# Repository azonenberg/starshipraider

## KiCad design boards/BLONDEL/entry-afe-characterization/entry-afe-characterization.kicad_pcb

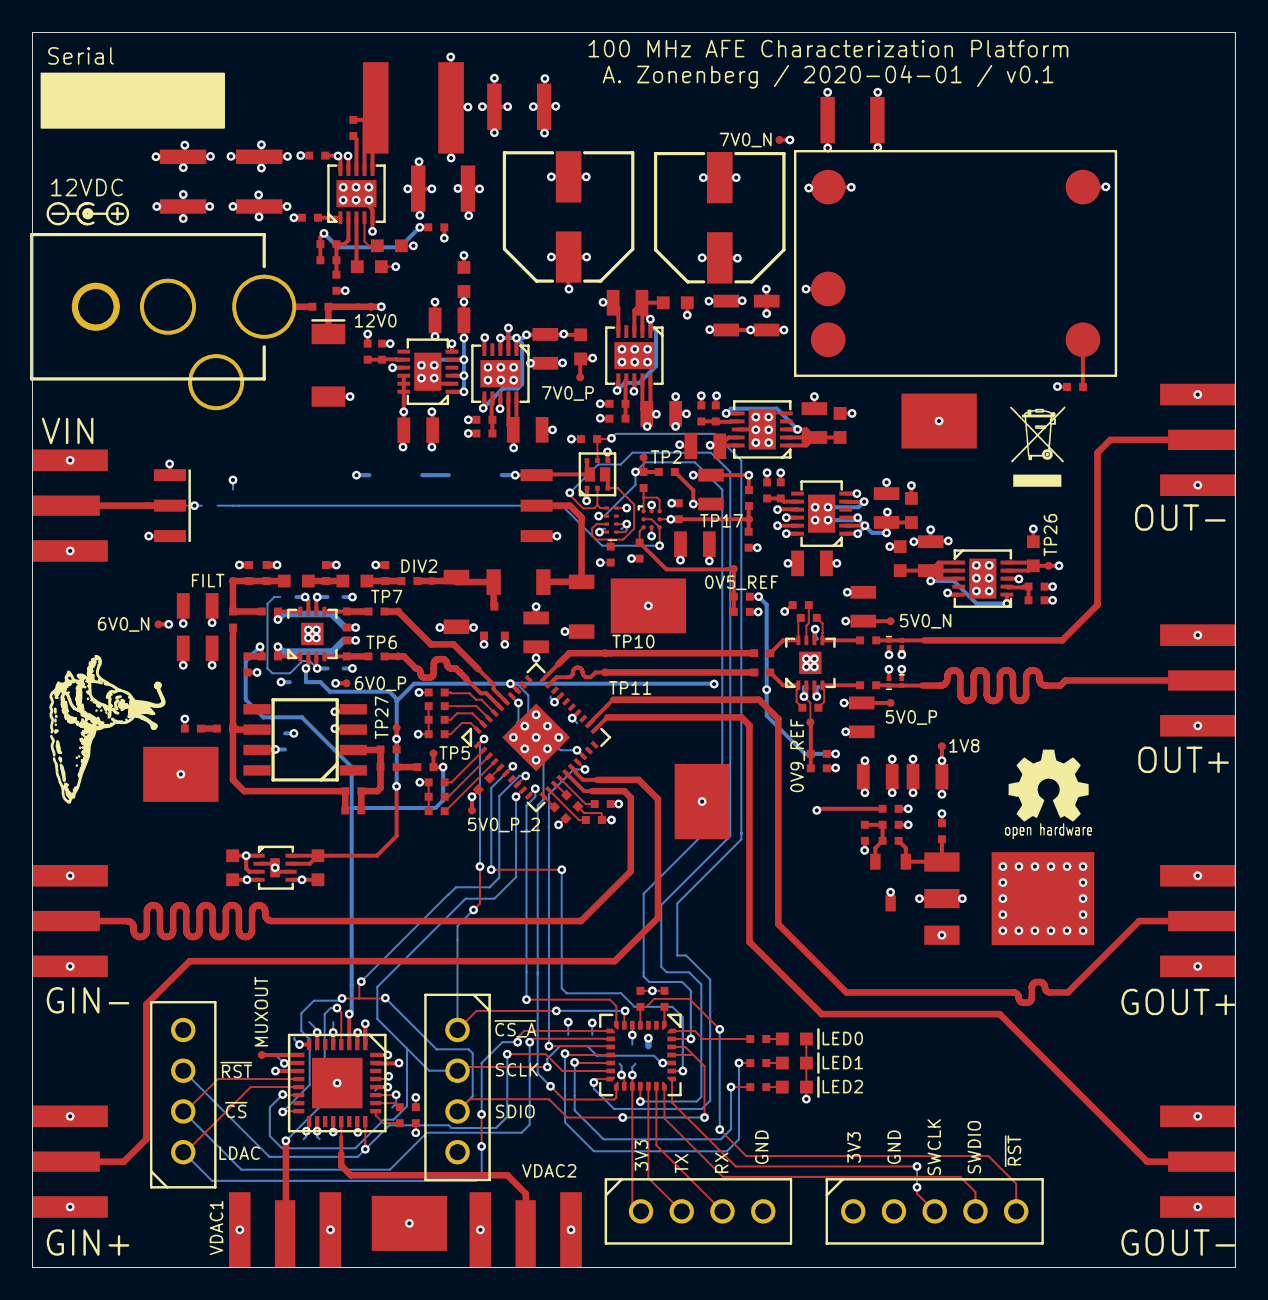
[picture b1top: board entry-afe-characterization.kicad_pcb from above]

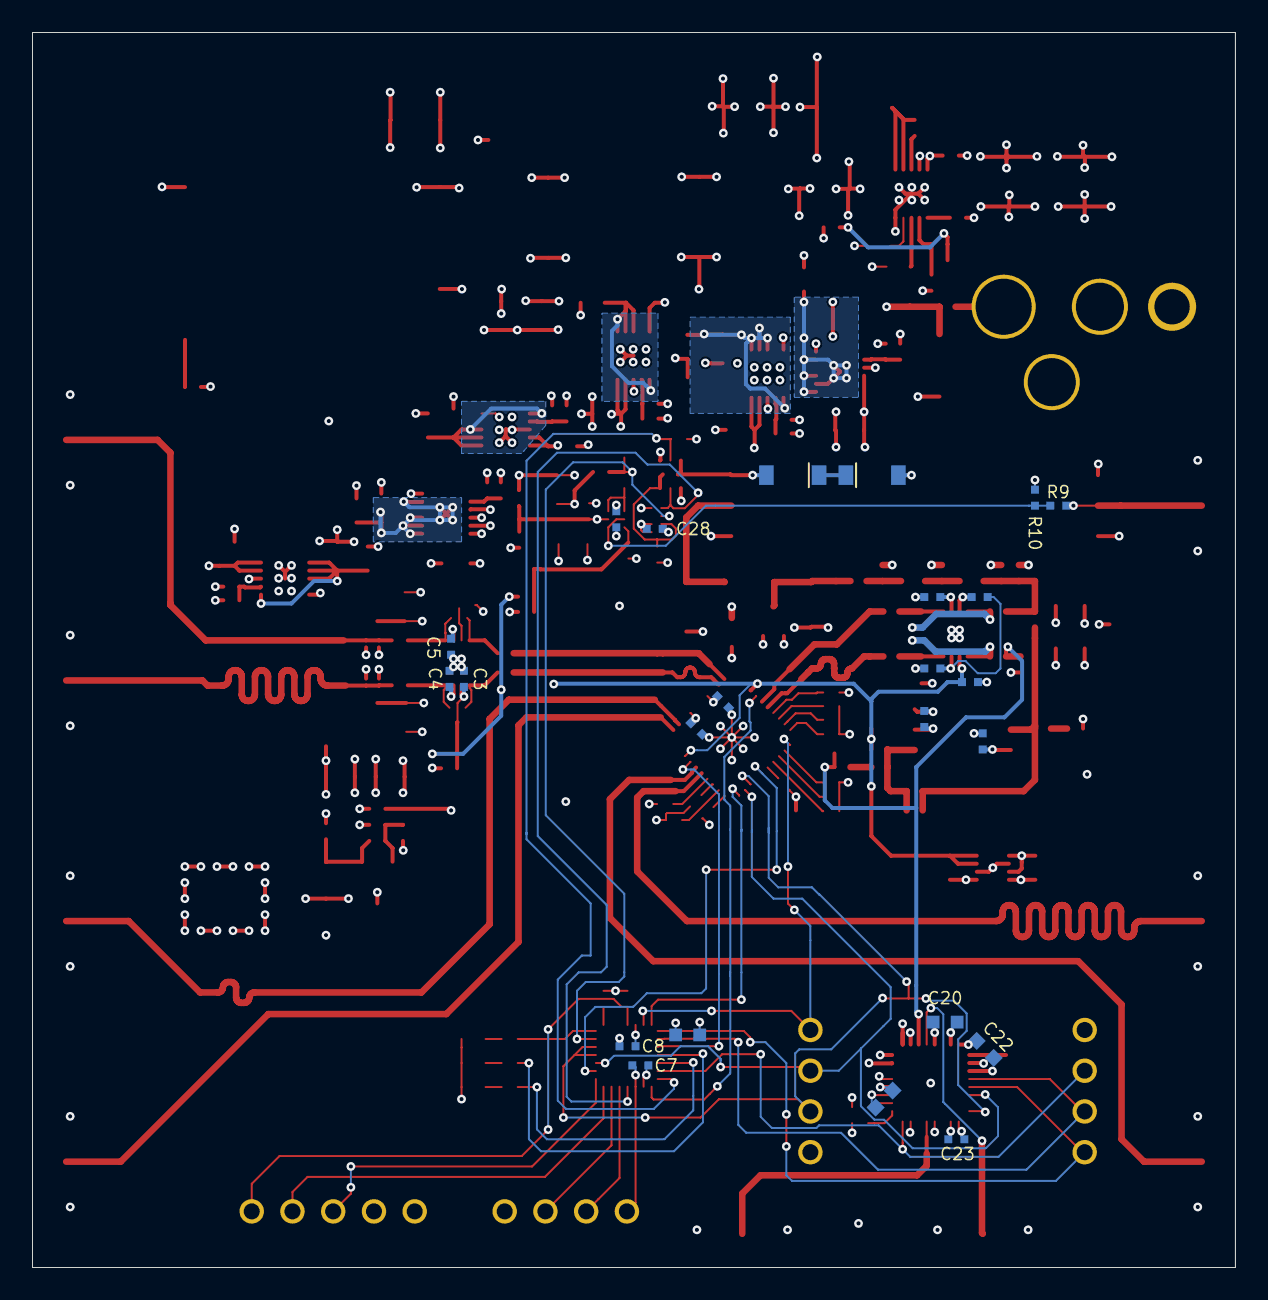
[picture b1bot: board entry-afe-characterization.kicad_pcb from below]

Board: 4 copper layers, 75.0 x 77.0 mm, 226 parts (24 on the bottom side), 116 nets.

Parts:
C1: 13 pF; EIA_0402_CAP_NOSILK
C2: 27 pF; EIA_0402_CAP_NOSILK
C3, C7, C8, C15, C28, C42, C43, C46, C73, C74: 0.47 uF; EIA_0402_CAP_NOSILK
C4, C5, C18, C19, C50, C59, C60, C66, C67: 0.47 uF 25V; EIA_0402_CAP_NOSILK
C6, C45: 4.7 uF; EIA_0603_CAP_NOSILK
C9, C13, C14, C23, C24, C25, C26, C32, C37, C68, C69: 0.1 uF; EIA_0402_CAP_NOSILK
C10, C11, C12, C27, C71, C72: 4.7 uF; EIA_0805_CAP_NOSILK
C16: 75 pF; EIA_0402_CAP_NOSILK
C17, C38, C39, C40, C41, C44, C51, C52, C55, C56, C57, C58, C61, C62: 4.7 uF 50V; EIA_0805_CAP_NOSILK
C20, C21, C22, C33: 1 uF; EIA_0603_CAP_NOSILK
C29, C30, C54: 10 uF; EIA_1210_CAP_NOSILK
C31: 3300 pF; EIA_0603_CAP_NOSILK
C34, C35: 22 uF; EIA_1210_CAP_NOSILK
C36: 10 pF; EIA_0402_CAP_NOSILK
C47: 2.2 uF; EIA_0603_CAP_NOSILK
C48: 330 pF; EIA_0603_CAP_NOSILK
C49, C53: 220 uF; CAP_AL_6.3MM_SMT
C63: 22 pF; EIA_0402_CAP_NOSILK
C64, C65: 22 uF; EIA_0805_CAP_NOSILK
C70: DNP; EIA_0402_CAP_NOSILK
D1: PDZ10BGWX; SOD123
D2: BAS21GWJ; SOD123
D3: NUP1301U; SOT323_3
D4, D5, D6, D7: NSR01F30MXT5G; DFN_2_0.62x0.32
D8: SMBJ12A; SMB
D9, D10, D11: GREEN; EIA_0603_LED
F1: 1A; EIA_0402_RES_NOSILK
FB1, FB2, FB3, FB4, FB5, FB6: MI0603J601R-10; EIA_0603_INDUCTOR_NOSILK
J1, J2, J3, J4, J5, J6, J7, J13, J14: SMA; CONN_SMA_EDGE_SAMTEC_SMA_J_P_H_ST_EM1
J8: Conn_01x05; CONN_HEADER_2.54MM_1x5
J9, J11, J12: Conn_01x04; CONN_HEADER_2.54MM_1x4
J10: CONN_3_PWROUT; CONN_CUI_PJ-058BH_HIPWR_BARREL_NOSLOT
K1: 9202-12-00; RELAY_COTO_9202
L1: 11 nH; EIA_0402_RES_NOSILK
L2: 51 nH; EIA_0603_INDUCTOR_NOSILK
L3: 91 nH; EIA_0603_INDUCTOR_NOSILK
L4: 4.7 uH; INDUCTOR_YUDEN_NR6028
Q1: SSM6N58NU; DFN_6_0.65MM_2x2MM_GDS
Q2: 2SA2039-TL-E; TO_253
R1, R3: CRCW1206150RFKEAHP; EIA_1206_CAP_NOSILK
R2: CRCW120637R4FKEAHP; EIA_1206_CAP_NOSILK
R4: 68 0.1%; EIA_0402_RES_NOSILK
R5, R6, R7, R8, R62: 330 0.1%; EIA_0402_RES_NOSILK
R9: 9.1K 1%; EIA_0402_RES_NOSILK
R10, R55: 1K 1%; EIA_0402_RES_NOSILK
R11, R12, R15, R16, R17, R18, R19, R20, R21, R22, R23, R24, R25, R26, R27, R34, R35, R36: 10K; EIA_0402_RES_NOSILK
R13, R14: 100 0.1%; EIA_0402_RES_NOSILK
R28, R29: 127 0.1%; EIA_0402_RES_NOSILK
R30, R31, R32, R33: 49.9; EIA_0402_RES_NOSILK
R37, R53: 1K; EIA_0402_RES_NOSILK
R38: 22.1K; EIA_0402_RES_NOSILK
R39: 180K; EIA_0402_RES_NOSILK
R40, R52: 470 1%; EIA_0402_RES_NOSILK
R41: 4.7K 1%; EIA_0402_RES_NOSILK
R42, R57, R58: 49.9K 1%; EIA_0402_RES_NOSILK
R43, R56: 60.4K 1%; EIA_0402_RES_NOSILK
R44, R63: 0; EIA_0402_RES_NOSILK
R45: 2.7K 1%; EIA_0402_RES_NOSILK
R46: 33K 1%; EIA_0402_RES_NOSILK
R47: 6.49K 1%; EIA_0402_RES_NOSILK
R48: 3.6K 1%; EIA_0402_RES_NOSILK
R49: 8.06K 1%; EIA_0402_RES_NOSILK
R50: 2K 1%; EIA_0402_RES_NOSILK
R51: 11.5K 1%; EIA_0402_RES_NOSILK
R54: 9.09K 1%; EIA_0402_RES_NOSILK
R59, R60, R64: 20K 0.1%; EIA_0402_RES_NOSILK
R61: 10K 0.1%; EIA_0402_RES_NOSILK
R65, R66, R67: 470; EIA_0402_RES_NOSILK
TP1, TP2, TP3, TP5, TP6, TP7, TP10, TP11, TP12, TP13, TP17, TP18, TP19, TP20, TP21, TP22, TP23, TP24, TP25, TP26, TP27, TP28, TP29: TESTPOINT; TESTPOINT_SMT_0.5MM
TP4, TP8, TP9, TP14, TP15: TESTCLIP; TESTPOINT_SMT_KEYSTONE_5016
U1, U6: LMH6552; DFN_8_0.5MM_3x3MM
U2: ADL5205; QFN_40_0.5MM_6x6MM
U3: LM393-DSBGA8; BGA_8_2x2_DEPOP1_0.5MM_TI_YZR
U4: STM32F031G6U6TR; QFN_28_0.5MM_4x4MM_NOPAD
U5: LTC2664; QFN_32_0.5MM_5x5MM
U7: 74LVC1G74-XSON8; DFN_8_0.5MM_2x1MM
U8: TPS54227-DRC; DFN_10_0.5MM_3x3MM
U9, U10, U11, U16: LT3042; DFN_10_0.5MM_3x3MM
U12: MCP1501T-25E/RW; DFN_8_0.5MM_2x2MM
U13, U15: LT3093; DFN_12_0.5MM_3x3MM
U14: PTN78000AAZ; MODULE_TI_PTN78000A
U17: TL431ACDBZR; SOT23_3
U18: OP07; SOIC_8_3.9MM

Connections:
/0V5_REF: C73.1, R49.2, R50.1, TP29.1, U3.C1
/0V9_REF: C3.1, R47.2, R48.1, TP28.1, U6.2
/1V8: C64.1, D4.1, D6.1, Q2.3, R40.2, R41.1, R52.1, TP12.1
/2V5_REF: C15.1, C48.1, R47.1, R49.1, R59.2, TP27.1, U1.2, U2.18, U2.33, U12.7, U12.8
/3V3: C6.1, C7.1, C8.1, C23.1, C45.1, C47.1, J8.1, J9.1, TP26.1, U4.5, U4.17, U5.18, U5.32, U11.9, U11.10, U12.1, U12.3
/5V0_N: C5.1, C9.2, C10.2, C22.1, C58.1, C65.2, C72.1, D3.1, R45.2, R54.1, TP18.1, U3.C2, U5.8, U5.PAD, U6.6, U15.10, U15.11, U15.12, U17.3
/5V0_P: C4.1, C9.1, C10.1, C20.1, C21.1, C27.1, C28.1, C40.1, C71.1, D3.2, R15.2, R36.1, R37.1, R40.1, TP24.1, U3.A2, U5.7, U5.28, U6.3, U7.8, U9.9, U9.10
/5V0_P_2: C17.1, C18.1, C19.1, C62.1, R16.2, R17.2, R26.1, TP25.1, U2.24, U2.27, U16.9, U16.10
/6V0_N: C12.2, C14.2, C57.1, C67.1, TP19.1, U1.6, U13.10, U13.11, U13.12, U18.4
/6V0_P: C11.1, C13.1, C41.1, C50.1, R12.2, TP23.1, U1.3, U10.9, U10.10, U18.7
/12V0: C29.1, C30.1, C37.2, C49.1, C51.1, C52.1, D1.2, D8.1, F1.2, K1.1, R11.2, TP21.1, U8.9, U8.10, U14.2
/Common mode shift/VGAIN_N: R14.2, TP11.1, U2.29
/Common mode shift/VGAIN_P: R13.2, TP10.1, U2.30
/Common mode shift/VOUT_N: D6.2, D7.1, J7.1, R33.1
/Common mode shift/VOUT_P: D4.2, D5.1, J6.1, R32.1
/DAC/DAC_REF: C24.1, U5.25
/DAC/DAC_REF_COMP: C25.1, U5.26
/DAC/MUXOUT: TP13.1, U5.9
/DAC/VDAC1: J13.1, U5.4
/DAC/VDAC2: J14.1, U5.21
/DAC_CS_N: J11.2, U4.9, U5.12
/DAC_LDAC: J11.1, U4.8, U5.13
/DAC_RST_N: J11.3, U4.13, U5.24
/GAIN2_PWRUP: U2.17, U4.10
/GAIN_PWRUP: U2.34, U4.15
/GND: C1.2, C2.2, C3.2, C4.2, C5.2, C6.2, C7.2, C8.2, C11.2, C12.1, C13.2, C14.1, C15.2, C16.2, C17.2, C18.2, C19.2, C20.2, C21.2, C22.2, C23.2, C24.2, C25.2, C26.2, C27.2, C28.2, C29.2, C30.2, C31.2, C33.2, C34.2, C35.2, C37.1, C38.2, C39.2, C40.2, C41.2, C42.2, C43.2, C44.2, C45.2, C46.2, C47.2, C48.2, C49.2, C50.2, C51.2, C52.2, C53.1, C54.2, C55.2, C56.2, C57.2, C58.2, C59.2, C60.2, C61.2, C62.2, C64.2, C65.1, C66.2, C67.2, C68.2, C69.2, C71.2, C72.2, C73.2, C74.2, D5.2, D7.2, D8.2, D9.1, D10.1, D11.1, J1.2, J2.2, J3.2, J4.2, J5.2, J6.2, J7.2, J8.2, J9.4, J10.2, J11.4, J12.4, J13.2, J14.2, K1.5, K1.6, Q1.S1, Q1.S2, Q2.2, Q2.4, R1.2, R3.2, R4.2, R10.2, R18.2, R19.2, R20.2, R21.2, R22.2, R23.2, R24.2, R25.2, R27.1, R34.1, R35.2, R38.2, R42.1, R43.1, R46.1, R48.2, R50.2, R55.2, R56.2, R57.2, R58.1, TP4.1, TP8.1, TP9.1, TP14.1, TP15.1, U1.PAD, U2.PAD, U4.16, U5.1, U5.2, U5.5, U5.10, U5.11, U5.17, U5.20, U5.23, U5.27, U5.29, U5.31, U6.PAD, U7.1, U7.2, U7.4, U8.5, U8.PAD, U9.5, U9.8, U9.PAD, U10.5, U10.8, U10.PAD, U11.5, U11.8, U11.PAD, U12.2, U12.4, U12.5, U12.6, U12.PAD, U13.6, U13.9, U14.5, U15.6, U15.9, U16.5, U16.8, U16.PAD, U18.3
/Gain Stage/GIN_N: J3.1, U2.15
/Gain Stage/GIN_P: J2.1, U2.16
/Gain Stage/GOUT_N: J5.1, U2.21
/Gain Stage/GOUT_P: J4.1, U2.22
/Gain Stage/VSHIFTED_N: R31.1, TP7.1, U2.35
/Gain Stage/VSHIFTED_P: R30.1, TP6.1, U2.36
/INPUT_RST: Q1.G2, R34.2, U4.14
/Input/COIL_N: D2.2, K1.2, Q1.D1
/Input/INPUT_RST_N: Q1.D2, R36.2, U7.7
/Input/VIN: J1.1, K1.3, R9.1
/Input/VIN_DIV2: D3.3, L1.2, R2.1, R3.1, TP1.1
/Input/VIN_DIV10: R9.2, R10.1, U3.B1, U3.C3
/Input/VIN_FILTERED: C16.1, L3.1, R4.1, R5.2, R62.1, TP3.1
/Input/VIN_SWITCHED: K1.4, R1.1, R2.2
/MCU/LED0: R65.2, U4.28
/MCU/LED1: R66.2, U4.11
/MCU/LED2: R67.2, U4.12
/MCU/RST_N: C26.1, J8.5, U4.4
/MCU/SWCLK: J8.3, U4.22
/MCU/SWDIO: J8.4, U4.21
/MCU/UART_RX: J9.3, U4.20
/MCU/UART_TX: J9.2, U4.19
/N0V5_REF: C74.1, R54.2, R55.1, TP17.1, U3.B3
/OVERVOLTAGE_N: R37.2, R53.1, TP2.1, U4.27, U7.6
/Power Supply/5V0_P_2_SET: C66.1, R58.2, U16.7
/Power Supply/5V0_P_SET: C42.1, R42.2, U9.7
/Power Supply/7V0_ADJ: R51.1, U14.4
/Power Supply/7V0_FB: C36.1, R38.1, R39.1, U8.2
/Power Supply/7V0_N: C53.2, C54.1, FB4.2, FB5.2, R51.2, TP20.1, U14.1
/Power Supply/7V0_N_1: C55.1, FB4.1, U13.1, U13.2, U13.3, U13.5, U13.PAD
/Power Supply/7V0_N_2: C56.1, FB5.1, U15.1, U15.2, U15.3, U15.5, U15.PAD
/Power Supply/7V0_P: C34.1, C35.1, FB1.2, FB2.2, FB3.2, FB6.2, L4.1, R44.1, TP22.1
/Power Supply/7V0_P_1: C38.1, FB1.1, U9.1, U9.2, U9.3, U9.6
/Power Supply/7V0_P_2: C39.1, FB2.1, U10.1, U10.2, U10.3, U10.6
/Power Supply/7V0_P_3: C44.1, FB3.1, U11.1, U11.2, U11.3, U11.6
/Power Supply/7V0_P_4: C61.1, FB6.1, U16.1, U16.2, U16.3, U16.6
/Power Supply/7V0_P_SW: C32.2, L4.2, U8.6, U8.7
/Power Supply/7V0_SENSE: C36.2, R39.2, R44.2
/RELAY_EN: Q1.G1, U4.18, U7.5
/SPI_CS_A_N: J12.1, U2.1, U4.6
/SPI_CS_B_N: U2.10, U4.7
/SPI_SCLK: J12.2, U2.9, U4.24, U5.14
/SPI_SDIO: J12.3, U2.8, U4.25, U4.26, U5.16
/VGA_PERF_MODE: U2.6, U4.23
/VIN_OFFSET: C69.1, R6.2, R60.2, TP5.1, U5.3
unnamed: C1.1, L1.1, L2.2
unnamed: C2.1, L2.1, L3.2
unnamed: C31.1, U8.4
unnamed: C32.1, U8.8
unnamed: C33.1, U8.3
unnamed: C43.1, R43.2, U10.7
unnamed: C46.1, R46.2, U11.7
unnamed: C59.1, R56.1, U13.8
unnamed: C60.1, R57.1, U15.8
unnamed: C63.1, Q2.1, R52.2, U17.1
unnamed: C63.2, R41.2, R45.1, U17.2
unnamed: C68.1, R63.1
unnamed: C70.1, R61.1, R62.2, R63.2, U18.6
unnamed: C70.2, R59.1, R61.2, R64.1, U18.2
unnamed: D1.1, D2.1
unnamed: D9.2, R65.1
unnamed: D10.2, R66.1
unnamed: D11.2, R67.1
unnamed: F1.1, J10.1
unnamed: R5.1, R8.2, U1.8
unnamed: R6.1, R7.2, U1.1
unnamed: R11.1, U8.1
unnamed: R12.1, U1.7
unnamed: R13.1, R29.1, U6.8
unnamed: R14.1, R28.1, U6.1
unnamed: R15.1, U6.7
unnamed: R16.1, U2.37
unnamed: R17.1, U2.14
unnamed: R18.1, U2.39
unnamed: R19.1, U2.38
unnamed: R20.1, U2.12
unnamed: R21.1, U2.13
unnamed: R22.1, U2.40
unnamed: R23.1, U2.11
unnamed: R24.1, U2.2
unnamed: R25.1, U2.3
unnamed: R26.2, U2.5
unnamed: R27.2, U2.4
unnamed: R28.2, R32.2, U6.4
unnamed: R29.2, R33.2, U6.5
unnamed: R7.1, R30.2, U1.4
unnamed: R8.1, R31.2, U1.5
unnamed: R35.1, U4.1
unnamed: R53.2, U3.A1, U3.A3
unnamed: R60.1, R64.2

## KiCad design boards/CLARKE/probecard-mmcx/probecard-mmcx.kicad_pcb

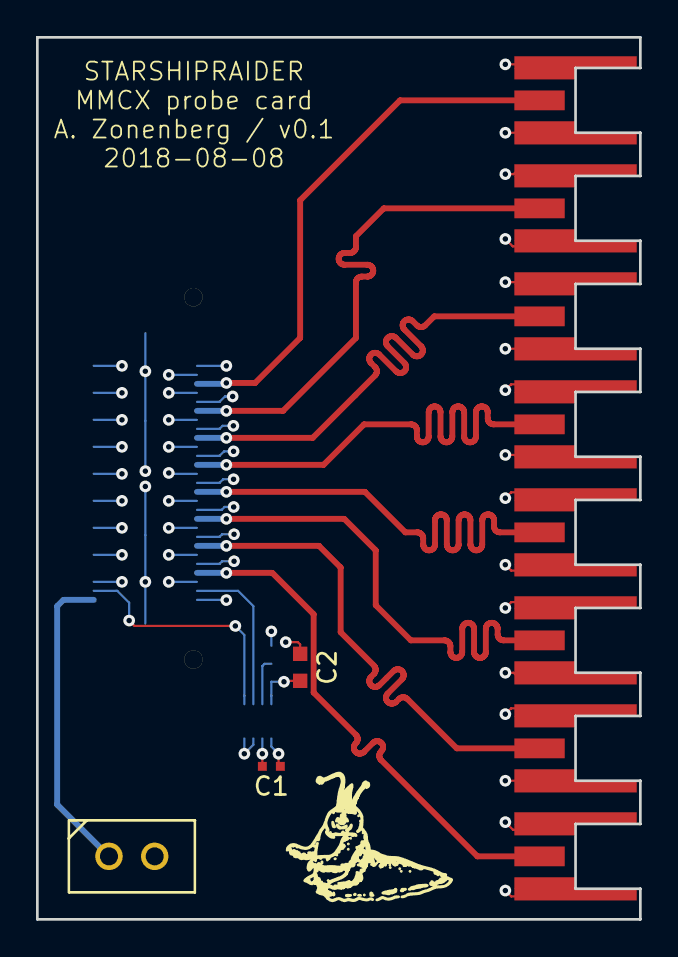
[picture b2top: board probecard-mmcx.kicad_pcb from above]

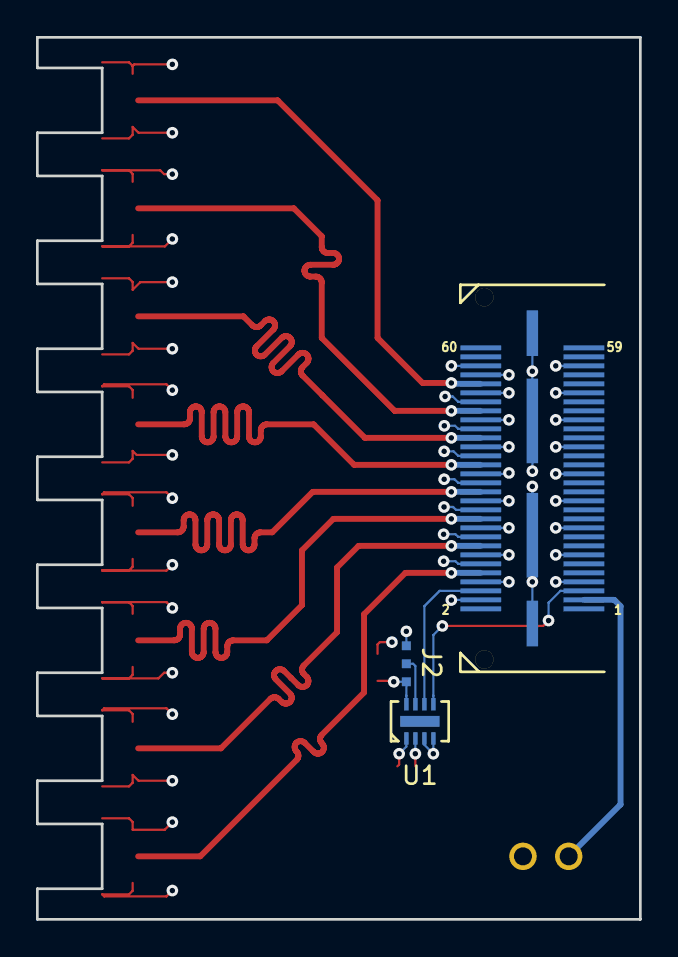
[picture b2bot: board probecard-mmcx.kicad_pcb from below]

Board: 4 copper layers, 33.5 x 49.0 mm, 14 parts (3 on the bottom side), 14 nets.

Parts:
C1: 0.47 uF; EIA_0402_CAP_NOSILK
C2: 4.7 uF; EIA_0603_CAP_NOSILK
J1: STARSHIPRAIDER_PROBE_MODULE; CONN_SAMTEC_QSH-030-01-L-D-A
J2: JUMPER_0402_SPDT; EIA_0402_JUMPER
J3, J4, J5, J6, J7, J8, J9, J10: CONN_COAXIAL; CONN_MMCX_J_P_H_ST_EM1
J11: CONN_01X02; CONN_HEADER_2.54MM_1x2
U1: 24C04-DFN8; DFN_8_0.5MM_2x3MM

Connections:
/3V3: C1.1, C2.1, J1.4, J2.1, U1.2, U1.8
/DQ0: J1.10, J3.1
/DQ1: J1.16, J4.1
/DQ2: J1.22, J5.1
/DQ3: J1.28, J6.1
/DQ4: J1.34, J7.1
/DQ5: J1.40, J8.1
/DQ6: J1.46, J9.1
/DQ7: J1.52, J10.1
/EEPROM_WP_N: J2.2, U1.7
/GND: C1.2, C2.2, J1.7, J1.8, J1.12, J1.13, J1.14, J1.18, J1.19, J1.20, J1.24, J1.25, J1.26, J1.30, J1.31, J1.32, J1.36, J1.37, J1.38, J1.42, J1.43, J1.44, J1.48, J1.49, J1.50, J1.54, J1.55, J1.56, J1.GND, J2.3, J3.2, J4.2, J5.2, J6.2, J7.2, J8.2, J9.2, J10.2, J11.2, U1.1, U1.3, U1.4
/I2C_SCL: J1.5, U1.5
/I2C_SDA: J1.6, U1.6
/VCCO_REF: J1.3, J11.1

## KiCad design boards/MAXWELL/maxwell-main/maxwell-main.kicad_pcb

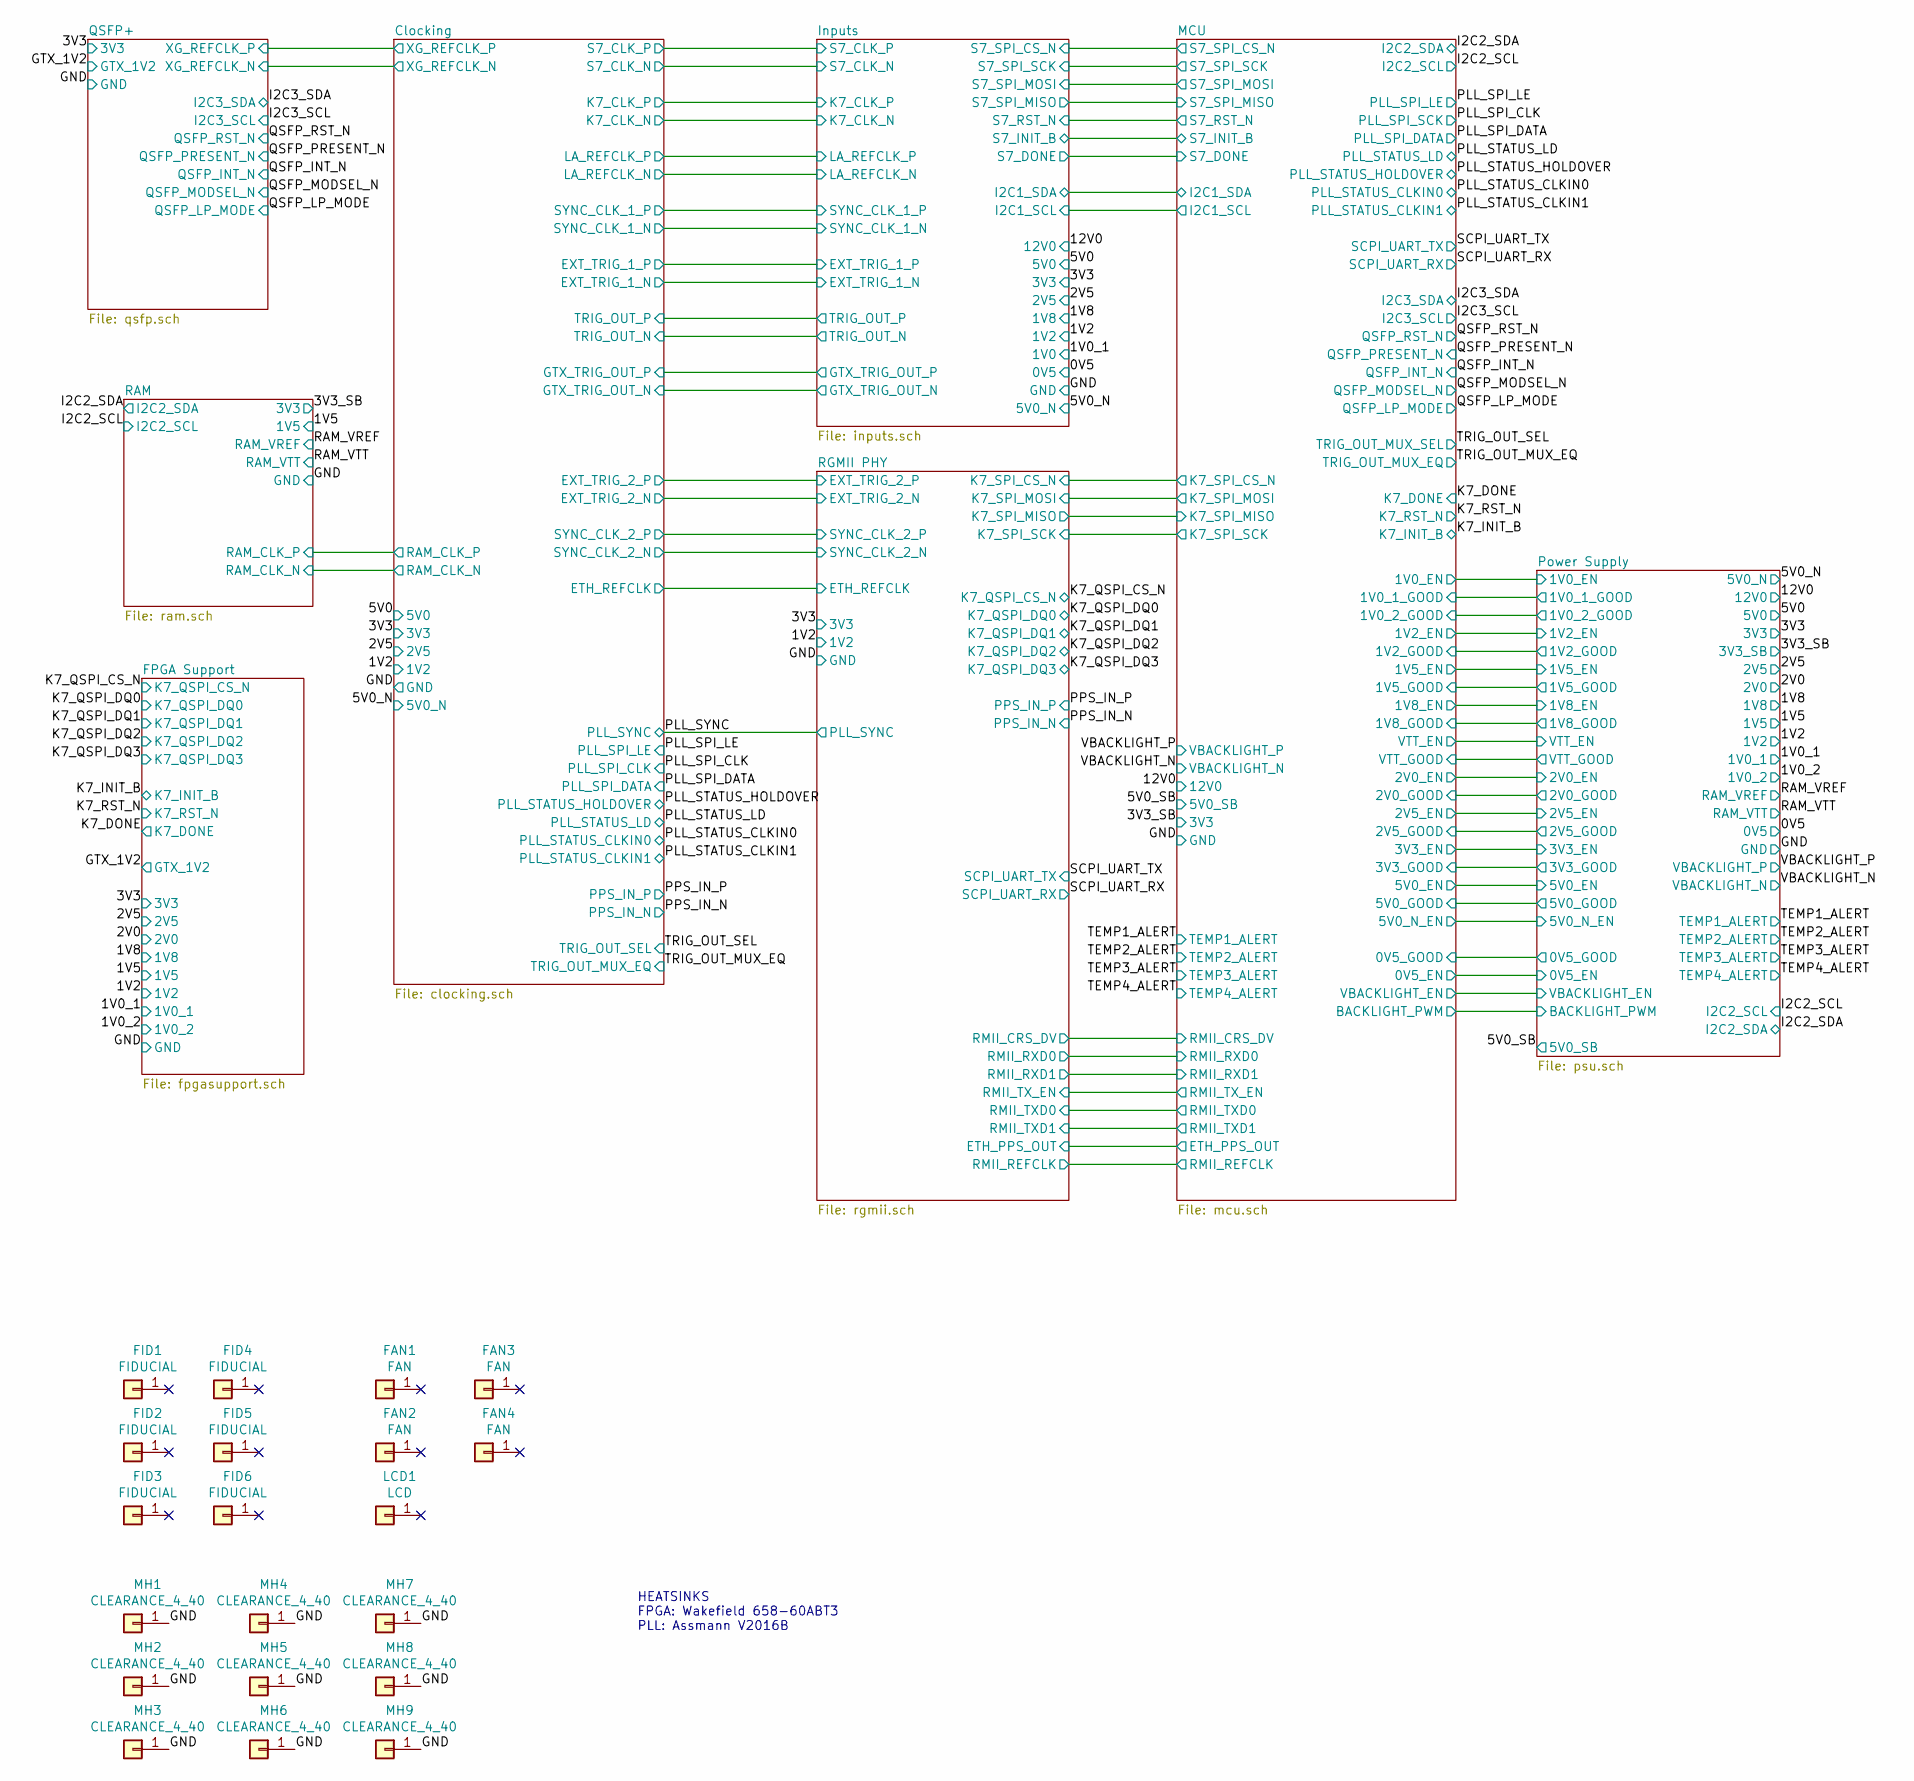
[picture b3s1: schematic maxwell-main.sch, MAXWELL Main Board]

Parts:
FAN1, FAN2, FAN3, FAN4: FAN; FAN_DELTA_EFB0412VHD-SP05
FID1, FID2, FID3, FID4, FID5, FID6: FIDUCIAL; FIDUCIAL_1MM
LCD1: LCD; LCD_MATRIX_MOP-TFT480116-38G-BLH-TPC
MH1, MH2, MH3, MH4, MH5, MH6, MH7, MH8, MH9: CLEARANCE_4_40; MECHANICAL_CLEARANCEHOLE_4_40

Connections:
/GND: MH1.1, MH2.1, MH3.1, MH4.1, MH5.1, MH6.1, MH7.1, MH8.1, MH9.1; also elsewhere on the board

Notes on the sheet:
HEATSINKS FPGA: Wakefield 658-60ABT3 PLL: Assmann V2016B

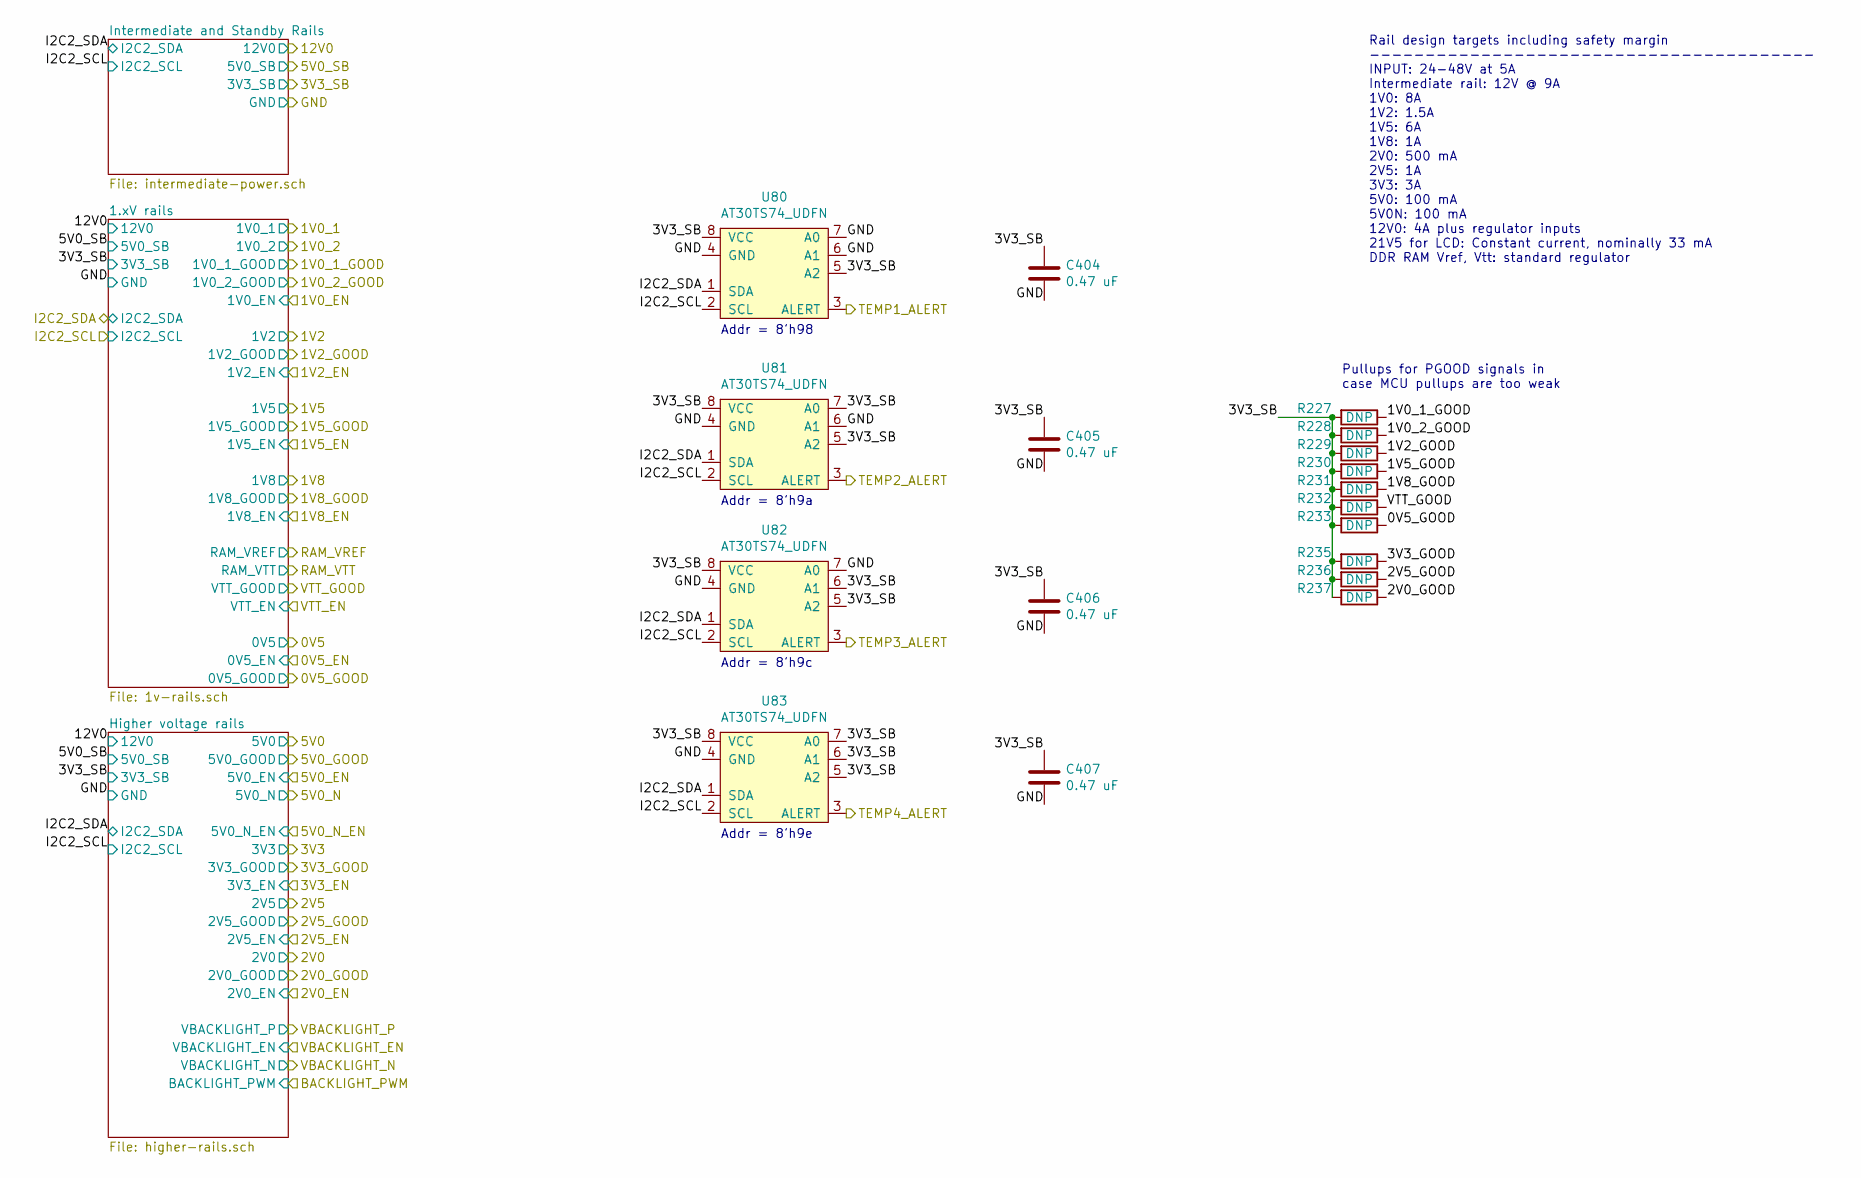
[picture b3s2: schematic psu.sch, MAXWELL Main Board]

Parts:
C404, C405, C406, C407: 0.47 uF; EIA_0402_CAP_NOSILK
R227, R228, R229, R230, R231, R232, R233, R235, R236, R237: DNP; EIA_0402_RES_NOSILK
U80, U81, U82, U83: AT30TS74_UDFN; DFN_8_0.5MM_2x3MM_TALL

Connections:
/3V3_SB: C404.1, C405.1, C406.1, C407.1, R227.2, R228.2, R229.2, R230.2, R231.2, R232.2, R233.2, R235.2, R236.2, R237.2, U80.5 (A2), U80.8 (VCC), U81.5 (A2), U81.7 (A0), U81.8 (VCC), U82.5 (A2), U82.6 (A1), U82.8 (VCC), U83.5 (A2), U83.6 (A1), U83.7 (A0), U83.8 (VCC); also elsewhere on the board
/GND: C404.2, C405.2, C406.2, C407.2, U80.4 (GND), U80.6 (A1), U80.7 (A0), U81.4 (GND), U81.6 (A1), U82.4 (GND), U82.7 (A0), U83.4 (GND); also elsewhere on the board
/I2C2_SCL: U80.2 (SCL), U81.2 (SCL), U82.2 (SCL), U83.2 (SCL); also elsewhere on the board
/I2C2_SDA: U80.1 (SDA), U81.1 (SDA), U82.1 (SDA), U83.1 (SDA); also elsewhere on the board
/MCU/0V5_GOOD: R233.1; also elsewhere on the board
/MCU/1V0_1_GOOD: R227.1; also elsewhere on the board
/MCU/1V0_2_GOOD: R228.1; also elsewhere on the board
/MCU/1V2_GOOD: R229.1; also elsewhere on the board
/MCU/1V5_GOOD: R230.1; also elsewhere on the board
/MCU/1V8_GOOD: R231.1; also elsewhere on the board
/MCU/2V0_GOOD: R237.1; also elsewhere on the board
/MCU/2V5_GOOD: R236.1; also elsewhere on the board
/MCU/3V3_GOOD: R235.1; also elsewhere on the board
/MCU/VTT_GOOD: R232.1; also elsewhere on the board
/TEMP1_ALERT: U80.3 (ALERT); also elsewhere on the board
/TEMP2_ALERT: U81.3 (ALERT); also elsewhere on the board
/TEMP3_ALERT: U82.3 (ALERT); also elsewhere on the board
/TEMP4_ALERT: U83.3 (ALERT); also elsewhere on the board

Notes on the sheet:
Rail design targets including safety margin ---------------------------------------- INPUT: 24-48V at 5A Intermediate rail: 12V @ 9A 1V0: 8A 1V2: 1.5A 1V5: 6A 1V8: 1A 2V0: 500 mA 2V5: 1A 3V3: 3A 5V0: 100 mA 5V0N: 100 mA 12V0: 4A plus regulator inputs 21V5 for LCD: Constant current, nominally 33 mA 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
Addr = 8'h98
Addr = 8'h9a
Addr = 8'h9c
Addr = 8'h9e
Pullups for PGOOD signals in case MCU pullups are too weak
